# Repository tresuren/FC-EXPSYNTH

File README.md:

# FC-EXPSYNTH

ファミコン拡張音源カセット(VRC6/VRC7/N163)を本物のチップで鳴らす中継カートリッジ(RP2350B)。PCからUSB-MIDIで、将来はmicroSDのVGMで演奏する計画。

## 構成
- `hardware/<Rev>/` — リビジョンごとのKiCadプロジェクト(回路図・基板・フットプリント・BOM・docs・生成スクリプト)
- `firmware/` — RP2350ファーム(現在 stage1_bus_test)

## バージョン管理
- リビジョンはフォルダ(`hardware/RevE1/` など)で管理。大きな設計変更は新フォルダ(RevE2…)で行う。
- 現在: **RevE5(ドラフト)** — 92x80mm、PPU バスと /IRQ を上部スロットへ直結(上のカセットのゲームが動く想定)、ゲーム/演奏モード切替、データバス双方向(ゲーム中の音源書き込みを記録用に読める)、全部品表面実装。DRC 未接続0。詳細は `hardware/RevE5/README.md`。
- RevE4 — RevE3 の電源まわりを修正(L1 をチップ横へ、電源配線を太く)。`hardware/RevE4/README.md`。
- RevE3 — RevE2から microSD・USB-C を基板端へ移動(ケース用)。`hardware/RevE3/README.md`。
- RevE2 — 92x60mm、表面SMD+裏面7個手半田、配線完了。`hardware/RevE2/` に残す。
- 過去: RevE1 — 配線7本未接続のため RevE2 で置き換え。`hardware/RevE1/` に残す。

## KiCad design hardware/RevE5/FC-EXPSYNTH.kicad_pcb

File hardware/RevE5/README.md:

# FC-EXPSYNTH (Rev.E5 draft) — 92x80mm、PPU直結・ゲームモード・データバス双方向

RevE4 を作り直した版。基板を 20mm 高くして、上に刺したカセットのゲームが動くように画面系(PPU)の線を通し、ゲーム中の音源書き込みを RP2350 が読めるようにした。部品は全部表面(JLCPCB の片面実装で全部載る。手半田は J11 など差し込み・直付けの部品だけ)。

## RevE4 からの変更点

### 回路(`FC-EXPSYNTH.kicad_sch`、`scripts/gen_sch.py`)
- **PPU バス 27 本(J10/J11 の 17〜29、47〜60 番)と /IRQ(15 番)を J10(接触指)⇔ J11(上部スロット)で直結**。ネット名 `PPU_*`、`CIRAM_*`、`IRQ_N`。
- **ゲーム/演奏モード切替**: `GAME` = GPIO30(R51 1k 経由)、R52 10k で +3V3 にプルアップ(**既定=ゲームモード**)。
  - RW_SYN = R/W AND NOT GAME(U14 の空きゲート + U15 の空きインバータ)
  - ROMSEL_EXP(J11 44番) = ROMSEL_N OR RW_SYN → ゲームモードでは上のカセットに /ROMSEL がそのまま届く。演奏モード(GPIO30 = Low)では書き込みだけ届く(RevE4 と同じ動作)。
- **データバス双方向化**: U13 を 74AHCT245(5V)→ **74LVC245(3.3V、B 側は 5V 入力対応)** に変更、DIR = R/W(読み出し: RP2350→ファミコン、書き込み: ファミコン→RP2350)。
  - **U17(74LVC1G02、新規)**: OE_N = NOT(RW_N OR OE1)。CPU の書き込みサイクルは常に U13 が開き、RP2350 がデータを読める(ゲーム中の音源レジスタ書き込みの記録用)。$8000 以上の読み出しは従来どおり EN_N で RP2350 が応答。
  - RP2350 に 5V が入らない構成(U13 の A 側は 3.3V 出力)。ファミコン側への出力は 3.3V(TTL の High 2.0V 以上)。
  - **ファーム側の注意**: CPU の書き込みサイクル中は ED0〜7(GPIO19〜26)を入力にしておくこと(U13 が RP2350 側へ出力するため。330Ω で保護はある)。
- テストパッド: TP7 = GAME、TP8 = IRQ_N(RevE4 の D0/A0 から変更)。
- 部品追加: U17、C42(U17 のパスコン)、R51、R52。部品数 99。

### 基板(`FC-EXPSYNTH.kicad_pcb`)
- **92x60mm → 92x80mm**(本体 0〜69.3mm、接触指 69.3〜80mm)。バッファ IC の列を y=52mm に置き、接触指までの配線帯を約 4mm → 約 14mm に拡大。
- **PPU の 27 本は裏面にまっすぐな縦の線(0.15mm、ロック)**: 接触指の上と J11 の下でビアを使い、裏面で 2 本 1 組(各ピンの ±0.6mm)で通す(`scripts/ppu_lanes.py`)。PPU_D4(60番)だけ USB-C の固定端子を避けて少し迂回。
- **裏面の部品なし**(RevE4 の裏 7 個のコンデンサは表面の 0402 に)。
- **水晶 Y1 を RP2350 の XIN/XOUT(30/31 番ピン)の約 4mm 下**へ。L1(コア電源インダクタ)は RevE4 と同じくピン 63 の隣。
- 電源ネット(+5V、+3V3、+1V1、VSYS、VBUS)に Power ネットクラス 0.25mm を設定して配線し、空きのある区間を最大 0.5mm に拡幅(`scripts/widen.py`)。
  - +5V: 0.5mm 57mm / 0.4mm 47mm / 0.3mm 62mm / 0.25mm 91mm(**全区間 0.25mm 以上**)
  - +3V3: 内層 In2 の面 + 配線(0.22mm 2mm 以外は 0.25mm 以上)
  - +1V1: 0.25〜0.5mm、VREG_LX 約 2mm
- 基板の縁から 0.45mm は配線・ビア禁止(自動配線が縁の規則を守らないため)。
- 部品名の文字 0.8mm / 線幅 0.12mm。

## 状態(正直な現状)
- DRC(`docs/drc.rpt`): **未接続 0・クリアランス違反 0・短絡 0・穴間隔違反 0・禁止エリア違反 0・基板端違反 0・余り線 0**。残りは警告: silk_over_copper 36 / silk_overlap 27 / lib_footprint_issues 99 / courtyards_overlap 1(J10 と J4、以前から)。
- **水晶の配線長: XIN 約 11mm、XOUT 約 13mm、C4 側 約 17mm**(Y1 自体はピンの直下だが、自動配線が C4 と R2 を少し離れた場所に置いた)。下は全面 GND 層。RevE4(約 23mm)より短いが、理想(数 mm)ではない。水晶まわりを固定して配線する案も 3 回試したが、RP2350 下側が詰まって 2〜7 本つながらなかったため、この版を採用。発振は実機で確認が必要。
- **ERC(回路図のルール検査)は未実施**(この環境の KiCad 7 の CLI に ERC がないため)。KiCad で開いて確認してほしい。
- 74LVC245 を 3.3V で使い、ファミコンのバスへ 3.3V で出す設計。ファミコン実機での読み出しタイミング・電圧の余裕は実機で確認が必要。
- J11(上部スロット)のフットプリントは仮寸法のまま(実物の 2x30 コネクタで要確認)。microSD、USB-C の実物寸法も未確認。
- LCSC 部品番号、JLCPCB 見積り、ファーム(モード切替・書き込み記録)は未着手。
- 上のカセットでゲームを動かすには: GAME = High(既定)、EN_N = High(既定)のまま。演奏モードでは RP2350 が GPIO30 を Low にしてから、本体のリセットボタンを押す想定。

## 図面
- `docs/pcb_render.png`(表面)、`docs/pcb_render_back.png`(裏面、左右反転表示)、`docs/fc_sch.pdf`(回路図)、`docs/drc.rpt`(DRC)、`BOM.csv`(部品表、`scripts/make_bom.py` で基板から生成)

## 再生成
1. `python3 scripts/gen_sch.py` → `kicad-cli sch export netlist -o fc.net FC-EXPSYNTH.kicad_sch`
2. `scripts/build_all.sh`(部品配置 `build_pcb.py` → `.kicad_pro` の規則を戻す → `ppu_lanes.py`)
3. `FR_JAR=... scripts/run_fr.sh`(Freerouting で自動配線 → `route.ses`)→ `python3 scripts/imp.py`
4. `HARD=1 python3 scripts/route_fix6.py <dir>`(残りの補修) → `scripts/widen.py`(電源線を太く)
自動配線は実行ごとに結果が変わる。確定した配線はこのフォルダの `FC-EXPSYNTH.kicad_pcb` を正とする(+3V3 の 50 番ピンと GPIO36 は手で補修済み)。

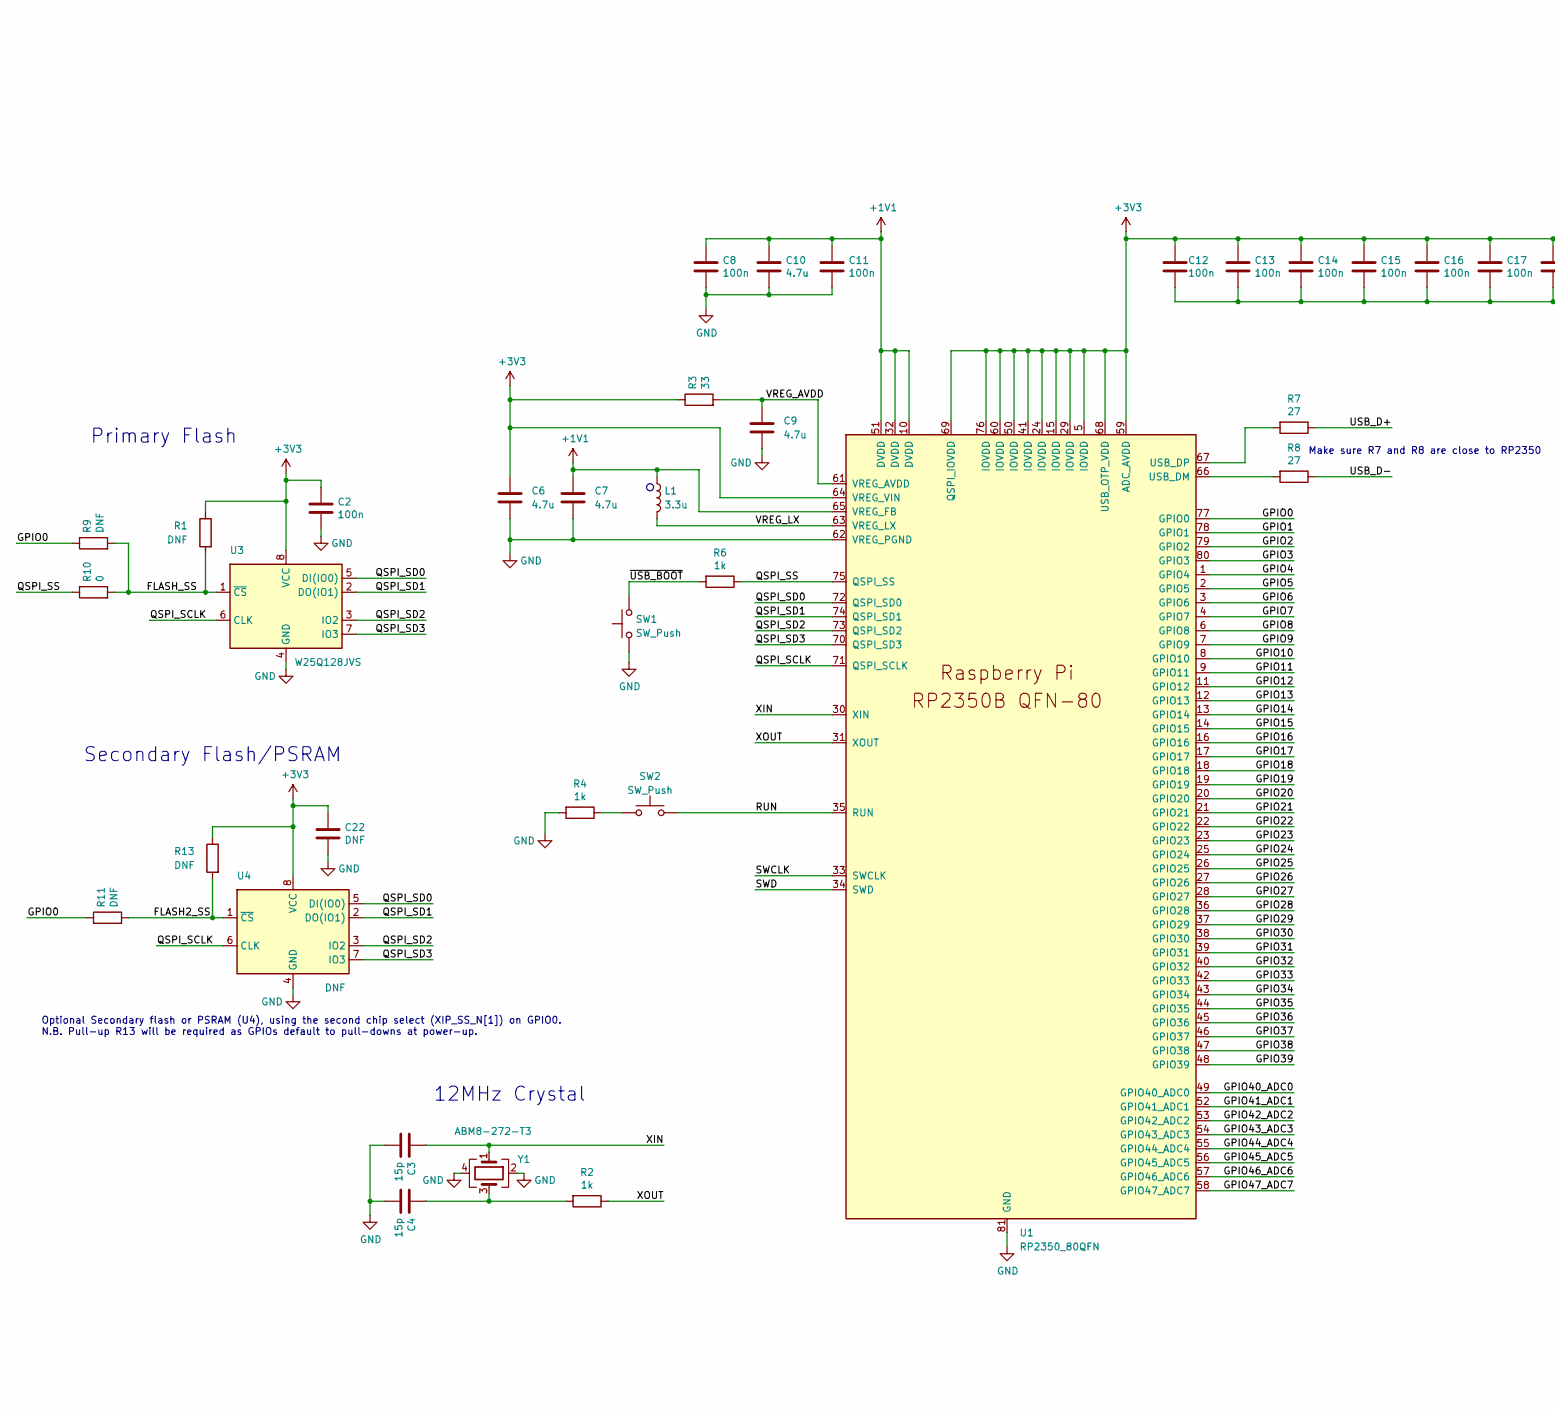
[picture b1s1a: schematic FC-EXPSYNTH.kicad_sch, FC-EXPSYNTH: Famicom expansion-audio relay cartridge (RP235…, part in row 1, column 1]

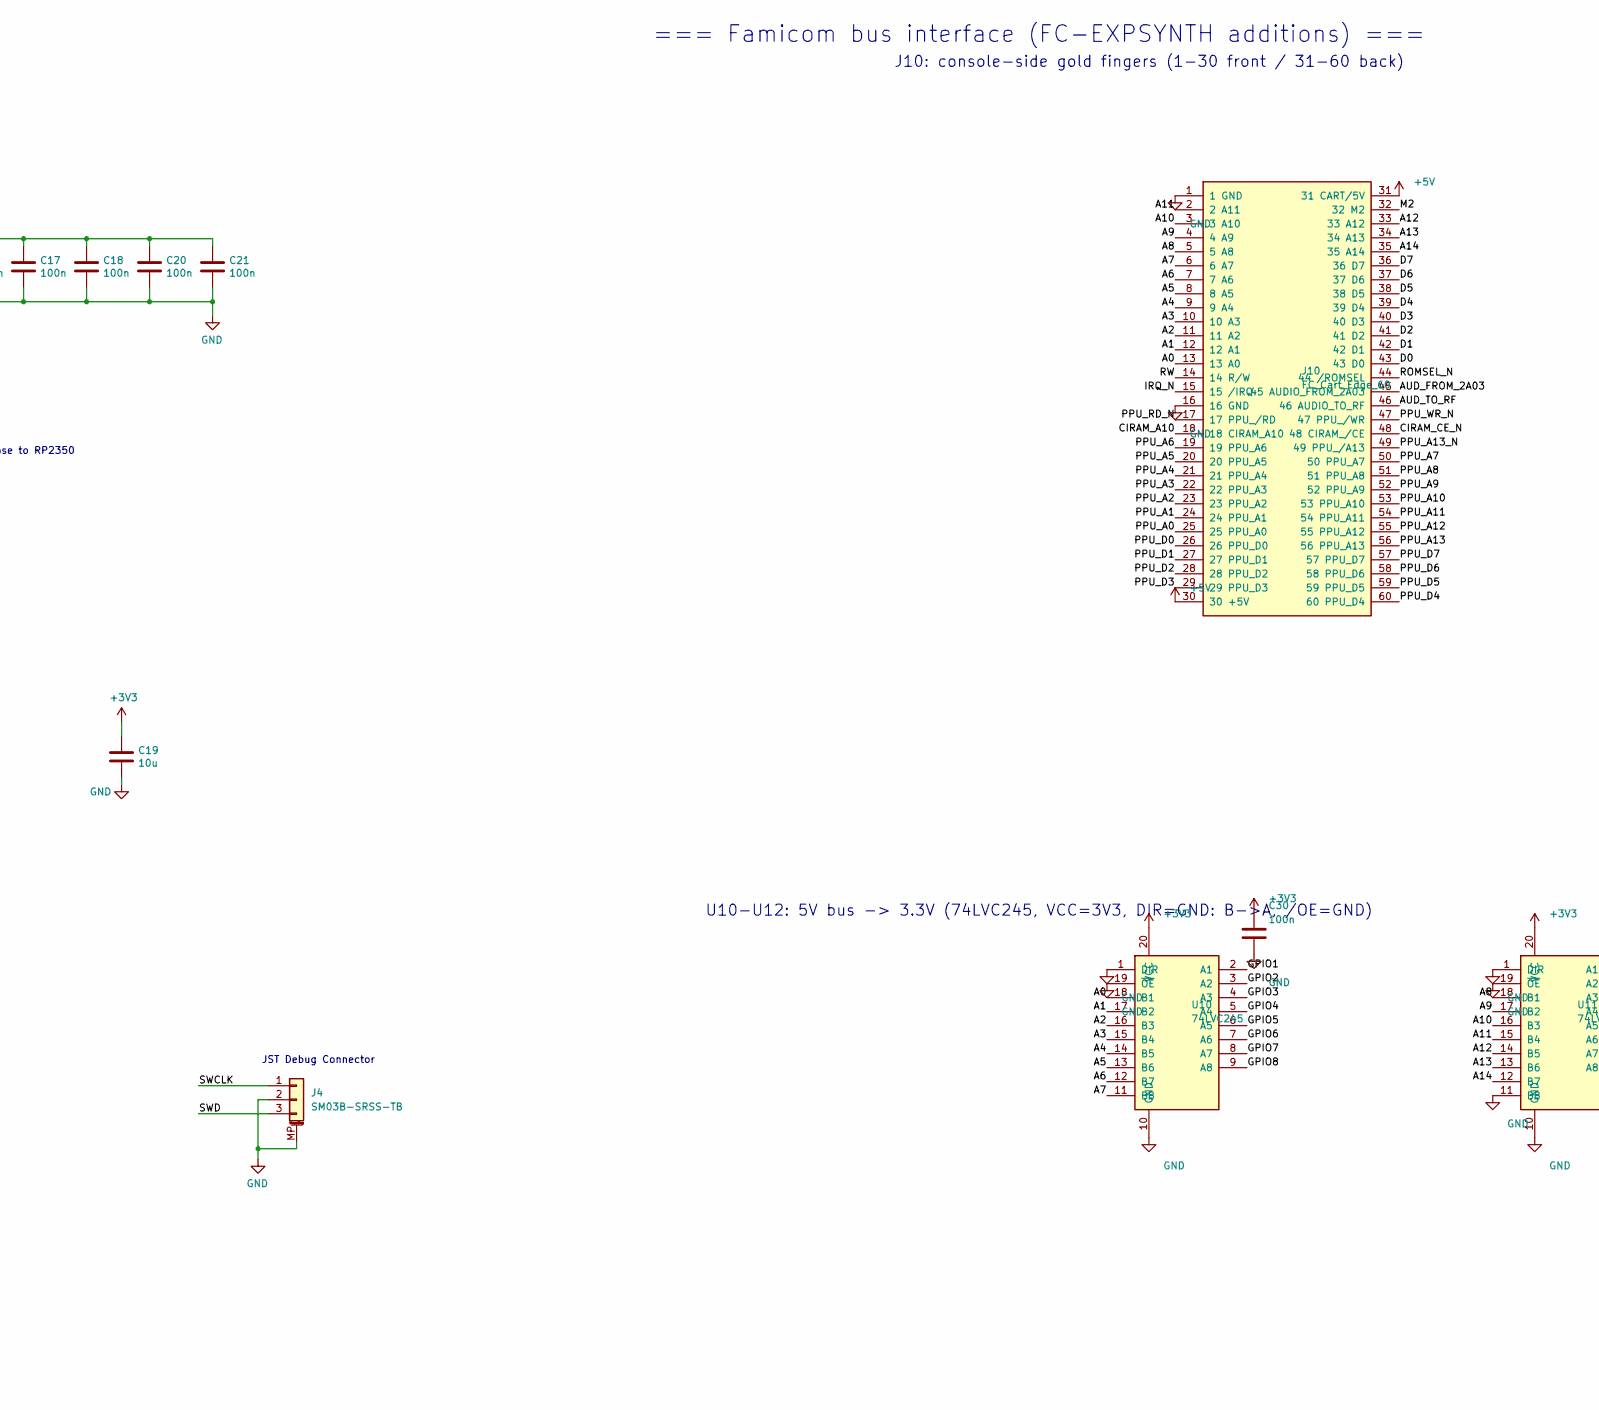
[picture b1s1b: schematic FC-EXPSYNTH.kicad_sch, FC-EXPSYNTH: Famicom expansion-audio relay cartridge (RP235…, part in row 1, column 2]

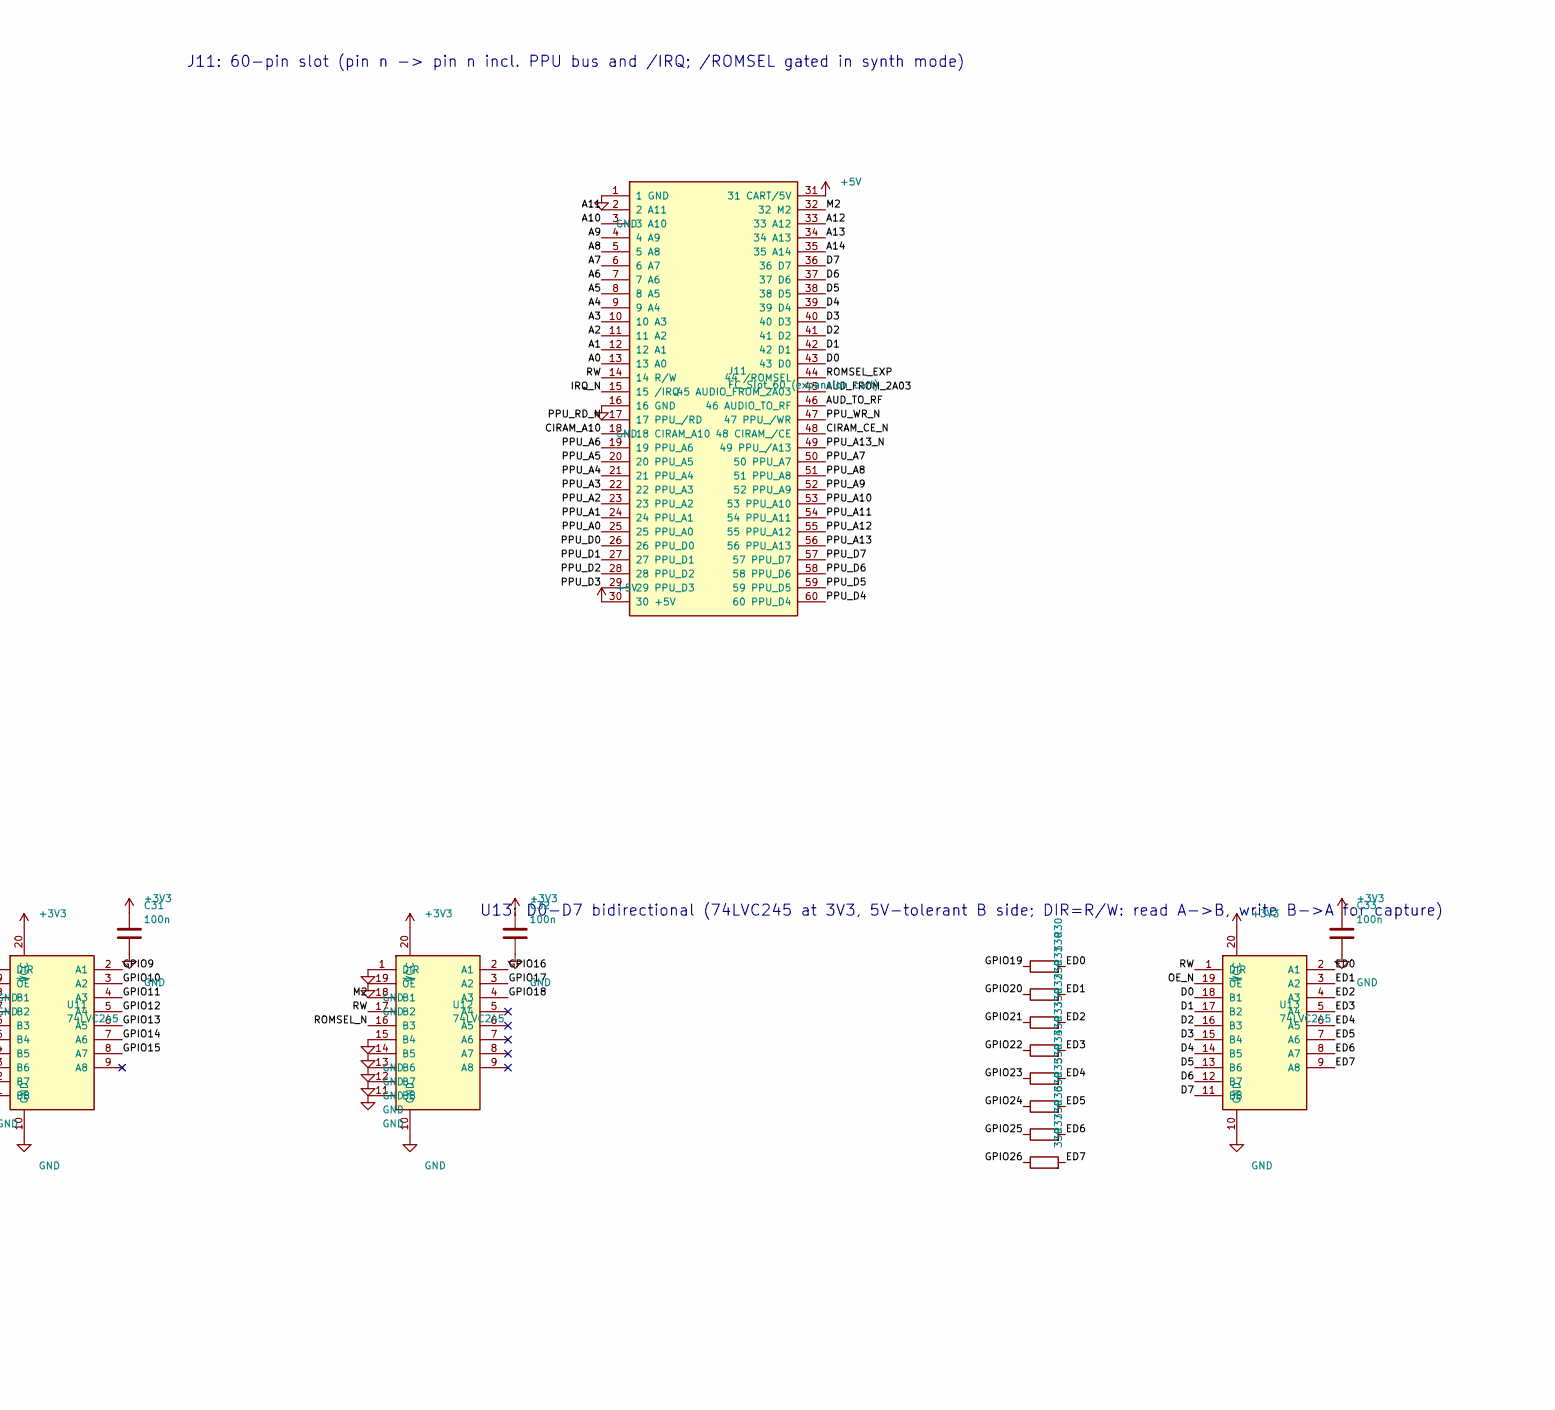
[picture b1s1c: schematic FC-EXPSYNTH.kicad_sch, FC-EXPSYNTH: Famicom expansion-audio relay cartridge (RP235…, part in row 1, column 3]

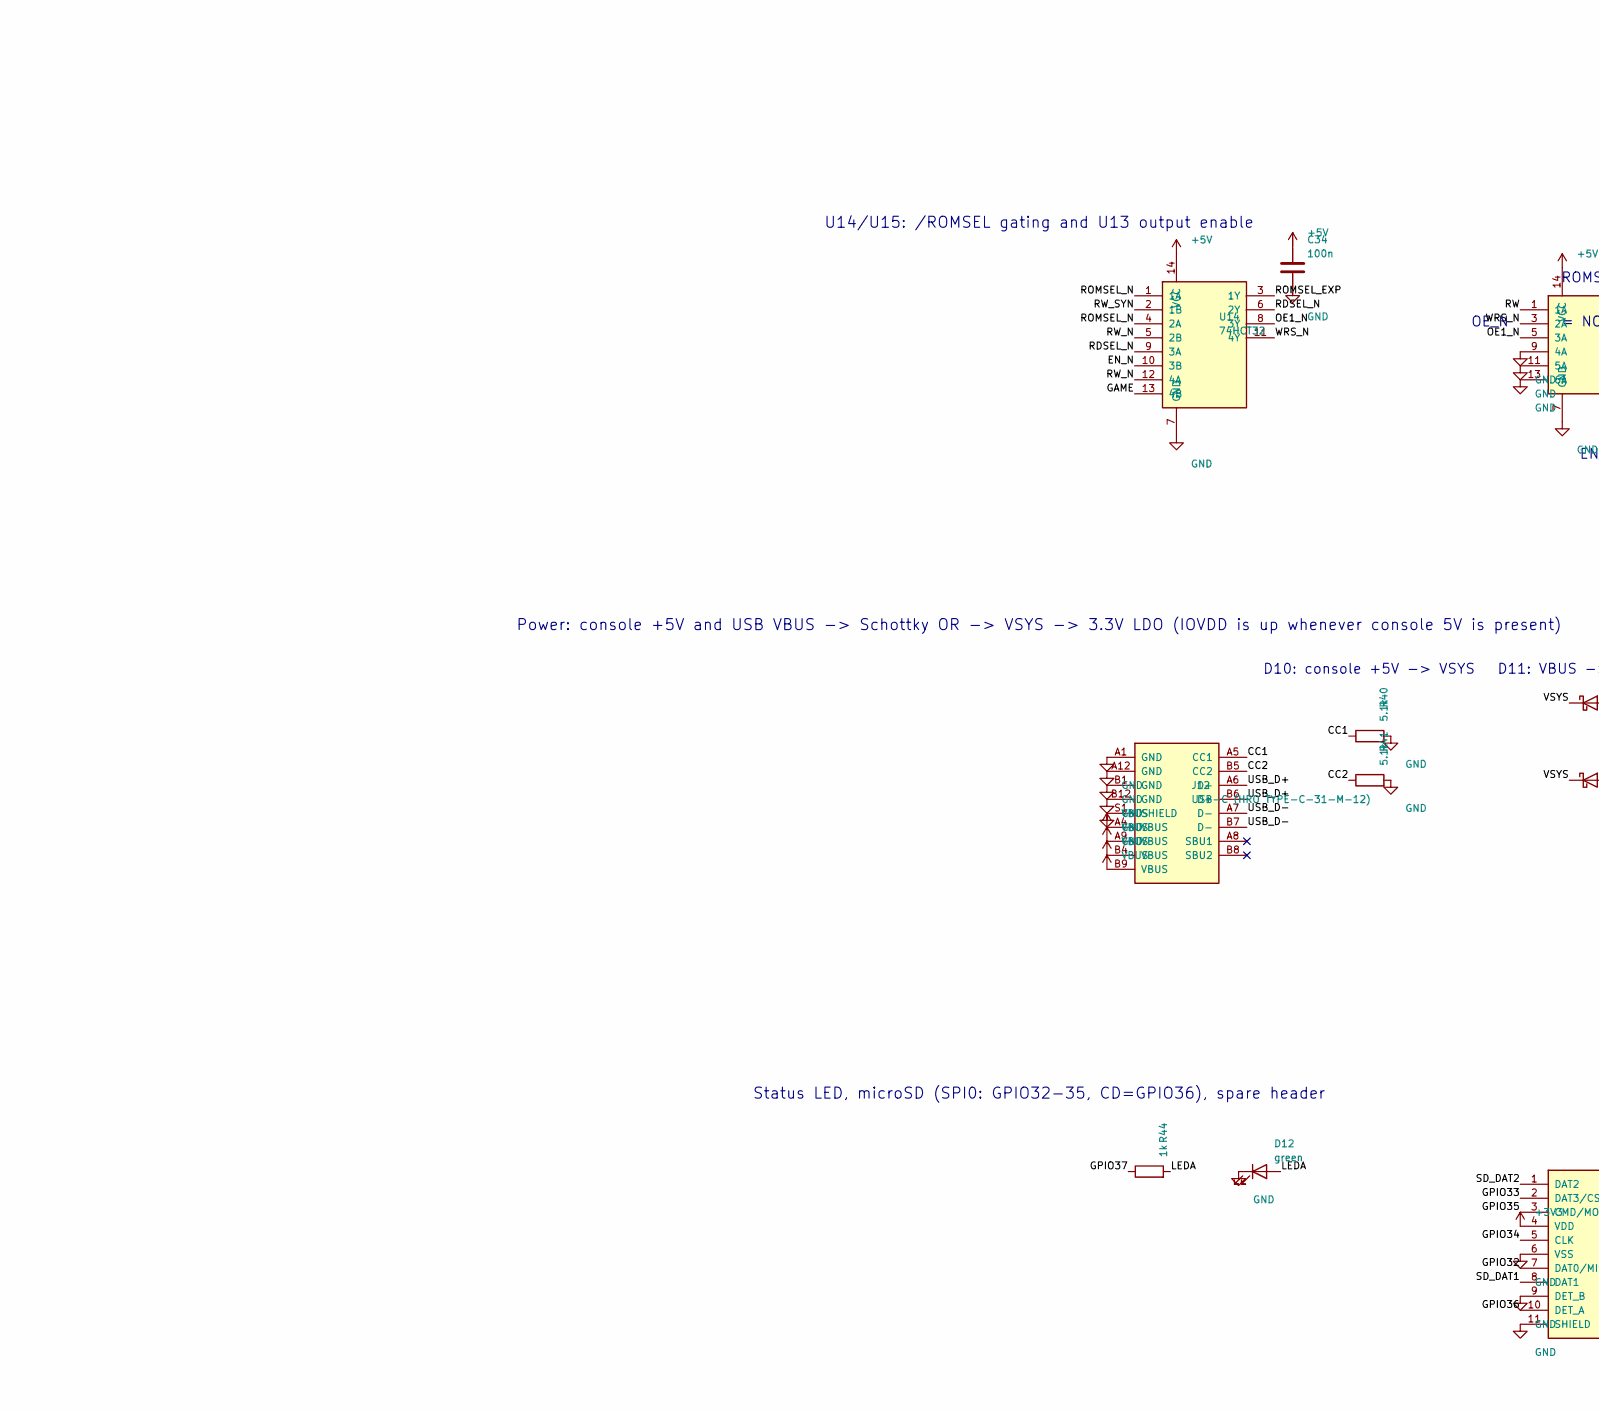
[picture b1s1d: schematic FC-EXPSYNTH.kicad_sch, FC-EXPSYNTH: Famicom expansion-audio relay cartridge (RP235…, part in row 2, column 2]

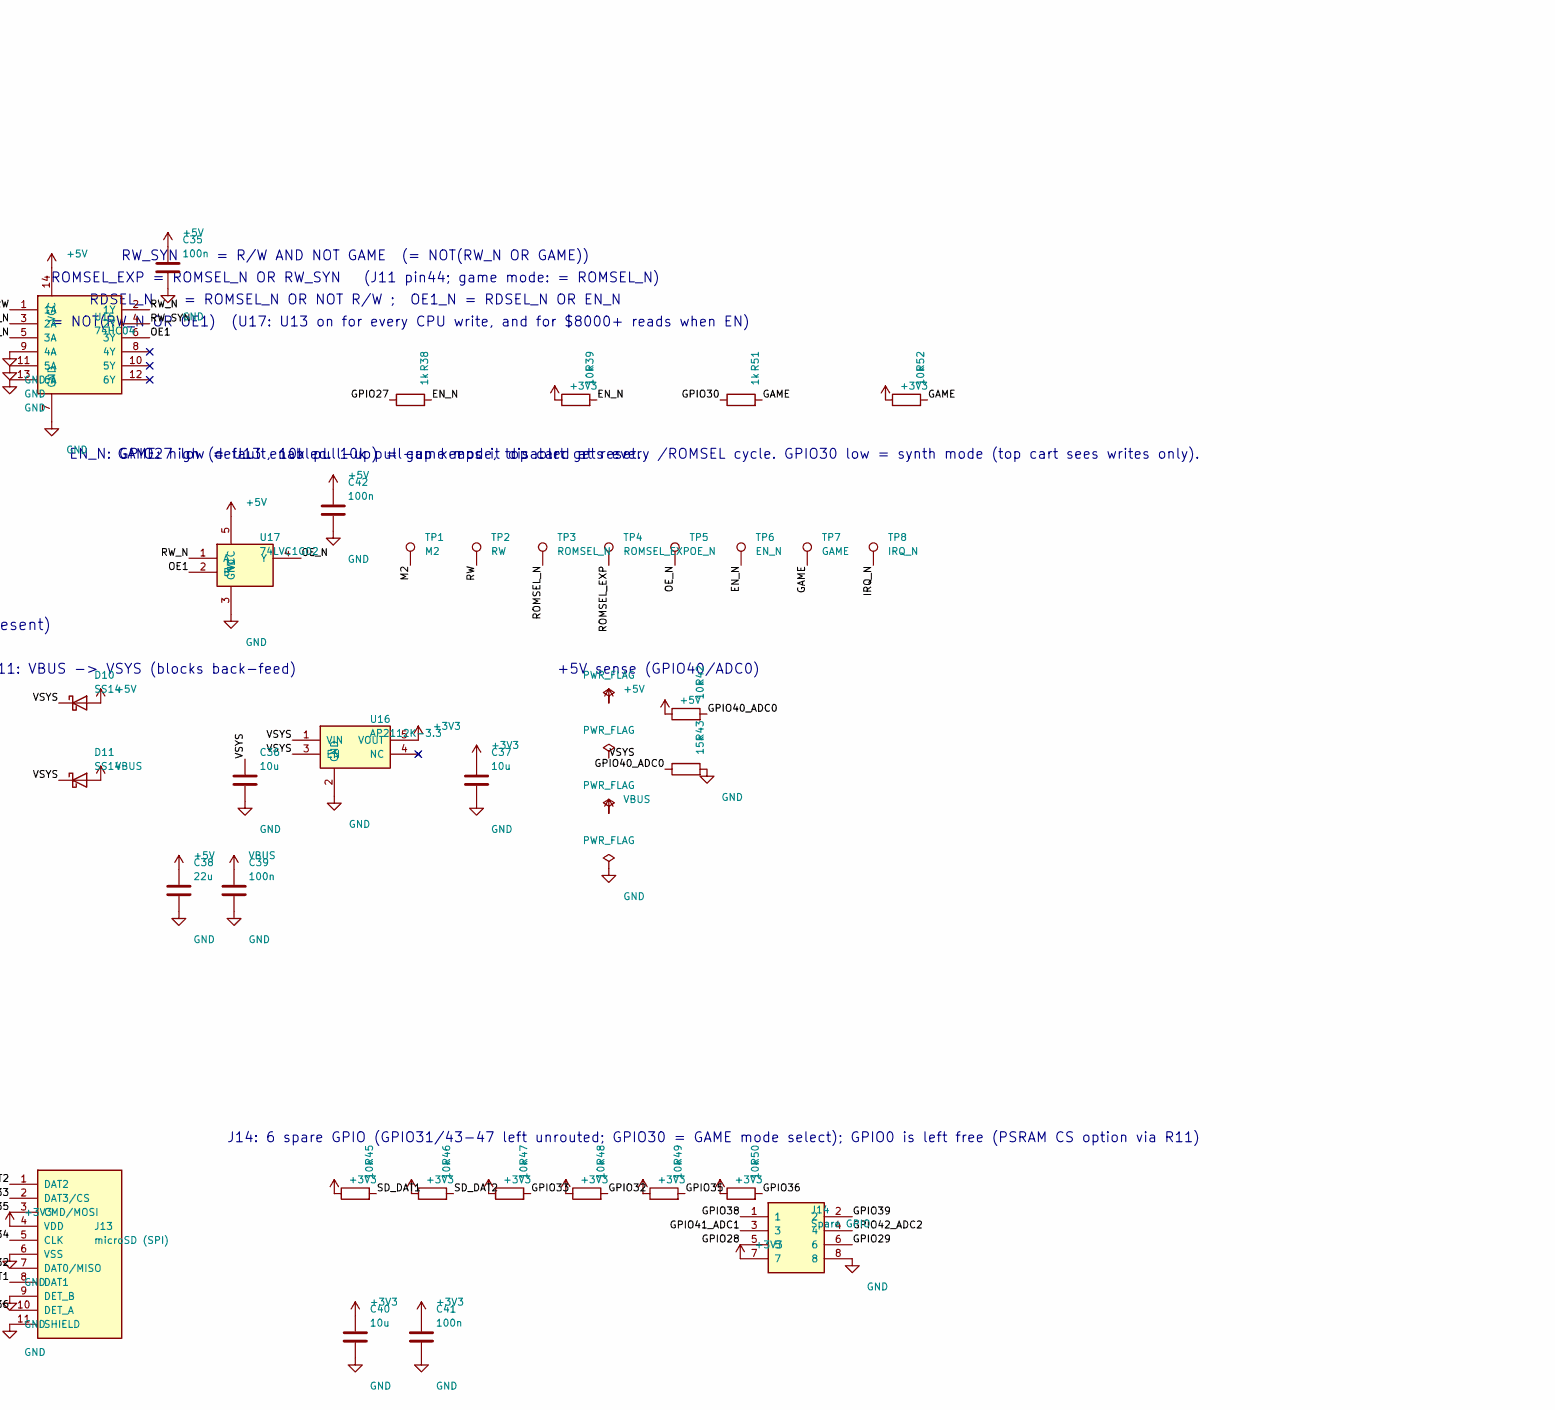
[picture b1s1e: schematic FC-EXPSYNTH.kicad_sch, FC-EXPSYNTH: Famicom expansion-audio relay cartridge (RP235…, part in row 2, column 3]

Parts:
C2, C8, C11, C12, C13, C14, C15, C16, C17, C18, C20, C21, C30, C31, C32, C33, C34, C35, C39, C41, C42: 100n; C_0402_1005Metric
C3, C4: 15p; C_0402_1005Metric
C6, C7: 4.7u; C_0402_1005Metric_small_pads
C9, C10: 4.7u; C_0402_1005Metric
C19, C36, C37, C40: 10u; C_0805_2012Metric
C22: DNF; C_0402_1005Metric
C38: 22u; C_0805_2012Metric
D10, D11: SS14; D_SMA
D12: green; LED_0603_1608Metric
J4: SM03B-SRSS-TB; JST_SH_SM03B-SRSS-TB_1x03-1MP_P1.00mm_Horizontal
J10: FC_Cart_Edge_60
J11: FC_Slot_60 (expansion cart); FC_Slot_60
J12: USB-C (HRO TYPE-C-31-M-12); USB_C_Receptacle_HRO_TYPE-C-31-M-12
J13: microSD (SPI); microSD_HC_Hirose_DM3AT-SF-PEJM5
J14: Spare GPIO; PinHeader_2x04_P2.54mm_Vertical
L1: 3.3u; L_pol_2016
R1, R9, R11, R13: DNF; R_0402_1005Metric
R2, R4, R6, R38, R44, R51: 1k; R_0402_1005Metric
R3: 33; R_0402_1005Metric
R7, R8: 27; R_0402_1005Metric
R10: 0; R_0402_1005Metric
R30, R31, R32, R33, R34, R35, R36, R37: 330; R_0402_1005Metric
R39, R42, R45, R46, R47, R48, R49, R50, R52: 10k; R_0402_1005Metric
R40, R41: 5.1k; R_0402_1005Metric
R43: 15k; R_0402_1005Metric
SW1, SW2: SW_Push; SW_Push_1P1T_NO_Vertical_Wuerth_434133025816
TP1: M2; TestPoint_Pad_D1.0mm
TP2: RW; TestPoint_Pad_D1.0mm
TP3: ROMSEL_N; TestPoint_Pad_D1.0mm
TP4: ROMSEL_EXP; TestPoint_Pad_D1.0mm
TP5: OE_N; TestPoint_Pad_D1.0mm
TP6: EN_N; TestPoint_Pad_D1.0mm
TP7: GAME; TestPoint_Pad_D1.0mm
TP8: IRQ_N; TestPoint_Pad_D1.0mm
U1: RP2350_80QFN; RP2350-QFN-80-1EP_10x10_P0.4mm_EP3.4x3.4mm_ThermalVias
U3: W25Q128JVS; SOIC-8_5.23x5.23mm_P1.27mm
U4: DNF; SOIC-8_5.23x5.23mm_P1.27mm
U10, U11, U12, U13: 74LVC245; TSSOP-20_4.4x6.5mm_P0.65mm
U14: 74HCT32; TSSOP-14_4.4x5mm_P0.65mm
U15: 74HC04; TSSOP-14_4.4x5mm_P0.65mm
U16: AP2112K-3.3; SOT-23-5
U17: 74LVC1G02; SOT-23-5
Y1: ABM8-272-T3; Crystal_SMD_3225-4Pin_3.2x2.5mm

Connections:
+1V1: C7.1, C8.1, C10.1, C11.1, L1.1, U1.10 (DVDD), U1.32 (DVDD), U1.51 (DVDD), U1.65 (VREG_FB)
+3V3: C2.1, C6.1, C12.1, C13.1, C14.1, C15.1, C16.1, C17.1, C18.1, C19.1, C20.1, C21.1, C22.1, C30.1, C31.1, C32.1, C33.1, C37.1, C40.1, C41.1, J13.4 (VDD), J14.7, R1.1, R3.1, R13.1, R39.1, R45.1, R46.1, R47.1, R48.1, R49.1, R50.1, R52.1, U1.5 (IOVDD), U1.15 (IOVDD), U1.24 (IOVDD), U1.29 (IOVDD), U1.41 (IOVDD), U1.50 (IOVDD), U1.59 (ADC_AVDD), U1.60 (IOVDD), U1.64 (VREG_VIN), U1.68 (USB_OTP_VDD), U1.69 (QSPI_IOVDD), U1.76 (IOVDD), U3.8 (VCC), U4.8 (VCC), U10.20 (VCC), U11.20 (VCC), U12.20 (VCC), U13.20 (VCC), U16.5 (VOUT)
+5V: C34.1, C35.1, C38.1, C42.1, D10.2 (A), J10.30 (30 +5V), J10.31 (31 CART/5V), J11.30 (30 +5V), J11.31 (31 CART/5V), R42.1, U14.14 (VCC), U15.14 (VCC), U17.5 (VCC)
/A0: J10.13 (13 A0), J11.13 (13 A0), U10.18 (B1)
/A1: J10.12 (12 A1), J11.12 (12 A1), U10.17 (B2)
/A2: J10.11 (11 A2), J11.11 (11 A2), U10.16 (B3)
/A3: J10.10 (10 A3), J11.10 (10 A3), U10.15 (B4)
/A4: J10.9 (9 A4), J11.9 (9 A4), U10.14 (B5)
/A5: J10.8 (8 A5), J11.8 (8 A5), U10.13 (B6)
/A6: J10.7 (7 A6), J11.7 (7 A6), U10.12 (B7)
/A7: J10.6 (6 A7), J11.6 (6 A7), U10.11 (B8)
/A8: J10.5 (5 A8), J11.5 (5 A8), U11.18 (B1)
/A9: J10.4 (4 A9), J11.4 (4 A9), U11.17 (B2)
/A10: J10.3 (3 A10), J11.3 (3 A10), U11.16 (B3)
/A11: J10.2 (2 A11), J11.2 (2 A11), U11.15 (B4)
/A12: J10.33 (33 A12), J11.33 (33 A12), U11.14 (B5)
/A13: J10.34 (34 A13), J11.34 (34 A13), U11.13 (B6)
/A14: J10.35 (35 A14), J11.35 (35 A14), U11.12 (B7)
/AUD_FROM_2A03: J10.45 (45 AUDIO_FROM_2A03), J11.45 (45 AUDIO_FROM_2A03)
/AUD_TO_RF: J10.46 (46 AUDIO_TO_RF), J11.46 (46 AUDIO_TO_RF)
/CC1: J12.A5 (CC1), R40.1
/CC2: J12.B5 (CC2), R41.1
/CIRAM_A10: J10.18 (18 CIRAM_A10), J11.18 (18 CIRAM_A10)
/CIRAM_CE_N: J10.48 (48 CIRAM_/CE), J11.48 (48 CIRAM_/CE)
/D0: J10.43 (43 D0), J11.43 (43 D0), U13.18 (B1)
/D1: J10.42 (42 D1), J11.42 (42 D1), U13.17 (B2)
/D2: J10.41 (41 D2), J11.41 (41 D2), U13.16 (B3)
/D3: J10.40 (40 D3), J11.40 (40 D3), U13.15 (B4)
/D4: J10.39 (39 D4), J11.39 (39 D4), U13.14 (B5)
/D5: J10.38 (38 D5), J11.38 (38 D5), U13.13 (B6)
/D6: J10.37 (37 D6), J11.37 (37 D6), U13.12 (B7)
/D7: J10.36 (36 D7), J11.36 (36 D7), U13.11 (B8)
/ED0: R30.2, U13.2 (A1)
/ED1: R31.2, U13.3 (A2)
/ED2: R32.2, U13.4 (A3)
/ED3: R33.2, U13.5 (A4)
/ED4: R34.2, U13.6 (A5)
/ED5: R35.2, U13.7 (A6)
/ED6: R36.2, U13.8 (A7)
/ED7: R37.2, U13.9 (A8)
/EN_N: R38.2, R39.2, TP6.1, U14.10 (3B)
/FLASH2_SS: R11.2, R13.2, U4.1 (~CS)
/FLASH_SS: R1.2, R9.2, R10.2, U3.1 (~CS)
/GAME: R51.2, R52.2, TP7.1, U14.13 (4B)
/GPIO0: R9.1, R11.1, U1.77 (GPIO0)
/GPIO1: U1.78 (GPIO1), U10.2 (A1)
/GPIO2: U1.79 (GPIO2), U10.3 (A2)
/GPIO3: U1.80 (GPIO3), U10.4 (A3)
/GPIO4: U1.1 (GPIO4), U10.5 (A4)
/GPIO5: U1.2 (GPIO5), U10.6 (A5)
/GPIO6: U1.3 (GPIO6), U10.7 (A6)
/GPIO7: U1.4 (GPIO7), U10.8 (A7)
/GPIO8: U1.6 (GPIO8), U10.9 (A8)
/GPIO9: U1.7 (GPIO9), U11.2 (A1)
/GPIO10: U1.8 (GPIO10), U11.3 (A2)
/GPIO11: U1.9 (GPIO11), U11.4 (A3)
/GPIO12: U1.11 (GPIO12), U11.5 (A4)
/GPIO13: U1.12 (GPIO13), U11.6 (A5)
/GPIO14: U1.13 (GPIO14), U11.7 (A6)
/GPIO15: U1.14 (GPIO15), U11.8 (A7)
/GPIO16: U1.16 (GPIO16), U12.2 (A1)
/GPIO17: U1.17 (GPIO17), U12.3 (A2)
/GPIO18: U1.18 (GPIO18), U12.4 (A3)
/GPIO19: R30.1, U1.19 (GPIO19)
/GPIO20: R31.1, U1.20 (GPIO20)
/GPIO21: R32.1, U1.21 (GPIO21)
/GPIO22: R33.1, U1.22 (GPIO22)
/GPIO23: R34.1, U1.23 (GPIO23)
/GPIO24: R35.1, U1.25 (GPIO24)
/GPIO25: R36.1, U1.26 (GPIO25)
/GPIO26: R37.1, U1.27 (GPIO26)
/GPIO27: R38.1, U1.28 (GPIO27)
/GPIO28: J14.5, U1.36 (GPIO28)
/GPIO29: J14.6, U1.37 (GPIO29)
/GPIO30: R51.1, U1.38 (GPIO30)
/GPIO31: U1.39 (GPIO31)
/GPIO32: J13.7 (DAT0/MISO), R48.2, U1.40 (GPIO32)
/GPIO33: J13.2 (DAT3/CS), R47.2, U1.42 (GPIO33)
/GPIO34: J13.5 (CLK), U1.43 (GPIO34)
/GPIO35: J13.3 (CMD/MOSI), R49.2, U1.44 (GPIO35)
/GPIO36: J13.10 (DET_A), R50.2, U1.45 (GPIO36)
/GPIO37: R44.1, U1.46 (GPIO37)
/GPIO38: J14.1, U1.47 (GPIO38)
/GPIO39: J14.2, U1.48 (GPIO39)
/GPIO40_ADC0: R42.2, R43.1, U1.49 (GPIO40_ADC0)
/GPIO41_ADC1: J14.3, U1.52 (GPIO41_ADC1)
/GPIO42_ADC2: J14.4, U1.53 (GPIO42_ADC2)
/GPIO43_ADC3: U1.54 (GPIO43_ADC3)
/GPIO44_ADC4: U1.55 (GPIO44_ADC4)
/GPIO45_ADC5: U1.56 (GPIO45_ADC5)
/GPIO46_ADC6: U1.57 (GPIO46_ADC6)
/GPIO47_ADC7: U1.58 (GPIO47_ADC7)
/IRQ_N: J10.15 (15 /IRQ), J11.15 (15 /IRQ), TP8.1
/LEDA: D12.2 (A), R44.2
/M2: J10.32 (32 M2), J11.32 (32 M2), TP1.1, U12.18 (B1)
/OE1: U15.6 (3Y), U17.2 (B)
/OE1_N: U14.8 (3Y), U15.5 (3A)
/OE_N: TP5.1, U13.19 (~OE), U17.4 (Y)
/PPU_A0: J10.25 (25 PPU_A0), J11.25 (25 PPU_A0)
/PPU_A1: J10.24 (24 PPU_A1), J11.24 (24 PPU_A1)
/PPU_A2: J10.23 (23 PPU_A2), J11.23 (23 PPU_A2)
/PPU_A3: J10.22 (22 PPU_A3), J11.22 (22 PPU_A3)
/PPU_A4: J10.21 (21 PPU_A4), J11.21 (21 PPU_A4)
/PPU_A5: J10.20 (20 PPU_A5), J11.20 (20 PPU_A5)
/PPU_A6: J10.19 (19 PPU_A6), J11.19 (19 PPU_A6)
/PPU_A7: J10.50 (50 PPU_A7), J11.50 (50 PPU_A7)
/PPU_A8: J10.51 (51 PPU_A8), J11.51 (51 PPU_A8)
/PPU_A9: J10.52 (52 PPU_A9), J11.52 (52 PPU_A9)
/PPU_A10: J10.53 (53 PPU_A10), J11.53 (53 PPU_A10)
/PPU_A11: J10.54 (54 PPU_A11), J11.54 (54 PPU_A11)
/PPU_A12: J10.55 (55 PPU_A12), J11.55 (55 PPU_A12)
/PPU_A13: J10.56 (56 PPU_A13), J11.56 (56 PPU_A13)
/PPU_A13_N: J10.49 (49 PPU_/A13), J11.49 (49 PPU_/A13)
/PPU_D0: J10.26 (26 PPU_D0), J11.26 (26 PPU_D0)
/PPU_D1: J10.27 (27 PPU_D1), J11.27 (27 PPU_D1)
/PPU_D2: J10.28 (28 PPU_D2), J11.28 (28 PPU_D2)
/PPU_D3: J10.29 (29 PPU_D3), J11.29 (29 PPU_D3)
/PPU_D4: J10.60 (60 PPU_D4), J11.60 (60 PPU_D4)
/PPU_D5: J10.59 (59 PPU_D5), J11.59 (59 PPU_D5)
/PPU_D6: J10.58 (58 PPU_D6), J11.58 (58 PPU_D6)
/PPU_D7: J10.57 (57 PPU_D7), J11.57 (57 PPU_D7)
/PPU_RD_N: J10.17 (17 PPU_/RD), J11.17 (17 PPU_/RD)
/PPU_WR_N: J10.47 (47 PPU_/WR), J11.47 (47 PPU_/WR)
/QSPI_SCLK: U1.71 (QSPI_SCLK), U3.6 (CLK), U4.6 (CLK)
/QSPI_SD0: U1.72 (QSPI_SD0), U3.5 (DI(IO0)), U4.5 (DI(IO0))
/QSPI_SD1: U1.74 (QSPI_SD1), U3.2 (DO(IO1)), U4.2 (DO(IO1))
/QSPI_SD2: U1.73 (QSPI_SD2), U3.3 (IO2), U4.3 (IO2)
/QSPI_SD3: U1.70 (QSPI_SD3), U3.7 (IO3), U4.7 (IO3)
/QSPI_SS: R6.1, R10.1, U1.75 (QSPI_SS)
/RDSEL_N: U14.6 (2Y), U14.9 (3A)
/ROMSEL_EXP: J11.44 (44 /ROMSEL), TP4.1, U14.3 (1Y)
/ROMSEL_N: J10.44 (44 /ROMSEL), TP3.1, U12.16 (B3), U14.1 (1A), U14.4 (2A)
/RUN: SW2.2, U1.35 (RUN)
/RW: J10.14 (14 R/W), J11.14 (14 R/W), TP2.1, U12.17 (B2), U13.1 (DIR), U15.1 (1A)
/RW_N: U14.5 (2B), U14.12 (4A), U15.2 (1Y), U17.1 (A)
/RW_SYN: U14.2 (1B), U15.4 (2Y)
/SD_DAT1: J13.8 (DAT1), R45.2
/SD_DAT2: J13.1 (DAT2), R46.2
/SWCLK: J4.1, U1.33 (SWCLK)
/SWD: J4.3, U1.34 (SWD)
/USB_D+: J12.A6 (D+), J12.B6 (D+), R7.1
/USB_D-: J12.A7 (D-), J12.B7 (D-), R8.1
/VREG_AVDD: C9.1, R3.2, U1.61 (VREG_AVDD)
/VREG_LX: L1.2, U1.63 (VREG_LX)
/VSYS: C36.1, D10.1 (K), D11.1 (K), U16.1 (VIN), U16.3 (EN)
/WRS_N: U14.11 (4Y), U15.3 (2A)
/XIN: C3.1, U1.30 (XIN), Y1.1
/XOUT: R2.1, U1.31 (XOUT)
/~USB_BOOT: R6.2, SW1.2
GND: C2.2, C3.2, C4.2, C6.2, C7.2, C8.2, C9.2, C10.2, C11.2, C12.2, C13.2, C14.2, C15.2, C16.2, C17.2, C18.2, C19.2, C20.2, C21.2, C22.2, C30.2, C31.2, C32.2, C33.2, C34.2, C35.2, C36.2, C37.2, C38.2, C39.2, C40.2, C41.2, C42.2, D12.1 (K), J4.2, J4.MP (MountPin), J10.1 (1 GND), J10.16 (16 GND), J11.1 (1 GND), J11.16 (16 GND), J12.A1 (GND), J12.A12 (GND), J12.B1 (GND), J12.B12 (GND), J12.S1 (SHIELD), J13.6 (VSS), J13.9 (DET_B), J13.11 (SHIELD), J14.8, R4.2, R40.2, R41.2, R43.2, SW1.1, U1.62 (VREG_PGND), U1.81 (GND), U3.4 (GND), U4.4 (GND), U10.1 (DIR), U10.10 (GND), U10.19 (~OE), U11.1 (DIR), U11.10 (GND), U11.11 (B8), U11.19 (~OE), U12.1 (DIR), U12.10 (GND), U12.11 (B8), U12.12 (B7), U12.13 (B6), U12.14 (B5), U12.15 (B4), U12.19 (~OE), U13.10 (GND), U14.7 (GND), U15.7 (GND), U15.9 (4A), U15.11 (5A), U15.13 (6A), U16.2 (GND), U17.3 (GND), Y1.2, Y1.4
unnamed: C4.1, R2.2, Y1.3
unnamed: R4.1, SW2.1
unnamed: R8.2, U1.66 (USB_DM)
unnamed: R7.2, U1.67 (USB_DP)
VBUS: C39.1, D11.2 (A), J12.A4 (VBUS), J12.A9 (VBUS), J12.B4 (VBUS), J12.B9 (VBUS)

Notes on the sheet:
Optional Secondary flash or PSRAM (U4), using the second chip select (XIP_SS_N[1]) on GPIO0. N.B. Pull-up R13 will be required as GPIOs default to pull-downs at power-up.
12MHz Crystal
Primary Flash
JST Debug Connector
Make sure R7 and R8 are close to RP2350
Secondary Flash/PSRAM
=== Famicom bus interface (FC-EXPSYNTH additions) ===
J10: console-side gold fingers (1-30 front / 31-60 back)
J11: 60-pin slot (pin n -> pin n incl. PPU bus and /IRQ; /ROMSEL gated in synth mode)
U10-U12: 5V bus -> 3.3V (74LVC245, VCC=3V3, DIR=GND: B->A, /OE=GND)
U13: D0-D7 bidirectional (74LVC245 at 3V3, 5V-tolerant B side; DIR=R/W: read A->B, write B->A for capture)
U14/U15: /ROMSEL gating and U13 output enable
GAME: high (default, 10k pull-up) = game mode, top cart gets every /ROMSEL cycle. GPIO30 low = synth mode (top cart sees writes only).
RW_SYN = R/W AND NOT GAME (= NOT(RW_N OR GAME))
ROMSEL_EXP = ROMSEL_N OR RW_SYN (J11 pin44; game mode: = ROMSEL_N)
RDSEL_N = ROMSEL_N OR NOT R/W ; OE1_N = RDSEL_N OR EN_N
OE_N = NOT(RW_N OR OE1) (U17: U13 on for every CPU write, and for $8000+ reads when EN)
EN_N: GPIO27 low = U13 enabled. 10k pull-up keeps it disabled at reset.
Power: console +5V and USB VBUS -> Schottky OR -> VSYS -> 3.3V LDO (IOVDD is up whenever console 5V is present)
D10: console +5V -> VSYS D11: VBUS -> VSYS (blocks back-feed)
+5V sense (GPIO40/ADC0)
Status LED, microSD (SPI0: GPIO32-35, CD=GPIO36), spare header
J14: 6 spare GPIO (GPIO31/43-47 left unrouted; GPIO30 = GAME mode select); GPIO0 is left free (PSRAM CS option via R11)

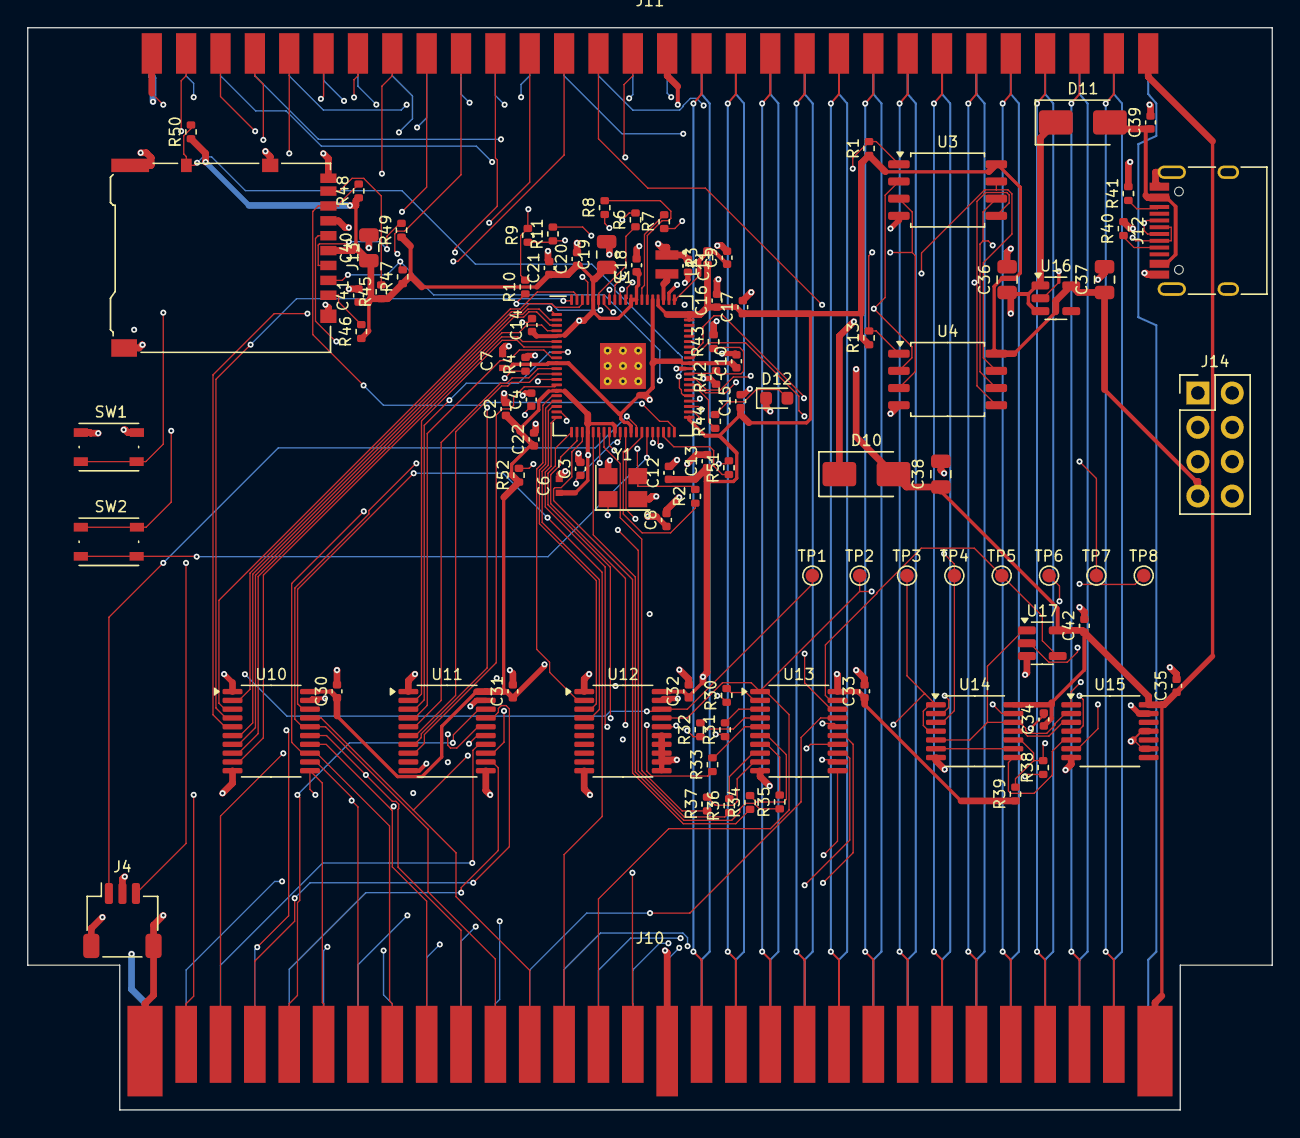
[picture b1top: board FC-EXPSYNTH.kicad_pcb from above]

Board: 4 copper layers, 92.0 x 80.0 mm, 99 parts (0 on the bottom side), 149 nets.

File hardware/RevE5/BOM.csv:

Designators,Qty,Value,Footprint,MPN/LCSC (UNVERIFIED - choose yourself)
C2 C8 C11 C12 C13 C14 C15 C16 C17 C18 C20 C21 C30 C31 C32 C33 C34 C35 C39 C41 C42,21,100n,C_0402_1005Metric,
C3 C4,2,15p,C_0402_1005Metric,
C6 C7,2,4.7u,C_0402_1005Metric_small_pads,
C9 C10,2,4.7u,C_0402_1005Metric,
C19 C36 C37 C40,4,10u,C_0805_2012Metric,
C22,1,DNF,C_0402_1005Metric,
C38,1,22u,C_0805_2012Metric,
D10 D11,2,SS14,D_SMA,
D12,1,green,LED_0603_1608Metric,
J4,1,SM03B-SRSS-TB,JST_SH_SM03B-SRSS-TB_1x03-1MP_P1.00mm_Horizontal,
J10,1,FC_Cart_Edge_60,FC_Cart_Edge_60,
J11,1,FC_Slot_60 (expansion cart),FC_Slot_60,hand-solder
J12,1,USB-C (HRO TYPE-C-31-M-12),USB_C_Receptacle_HRO_TYPE-C-31-M-12,
J13,1,microSD (SPI),microSD_HC_Hirose_DM3AT-SF-PEJM5,
J14,1,Spare GPIO,PinHeader_2x04_P2.54mm_Vertical,
L1,1,3.3u,L_pol_2016,
R1 R9 R11 R13,4,DNF,R_0402_1005Metric,
R2 R4 R6 R38 R44 R51,6,1k,R_0402_1005Metric,
R3,1,33,R_0402_1005Metric,
R7 R8,2,27,R_0402_1005Metric,
R10,1,0,R_0402_1005Metric,
R30 R31 R32 R33 R34 R35 R36 R37,8,330,R_0402_1005Metric,
R39 R42 R45 R46 R47 R48 R49 R50 R52,9,10k,R_0402_1005Metric,
R40 R41,2,5.1k,R_0402_1005Metric,
R43,1,15k,R_0402_1005Metric,
SW1 SW2,2,SW_Push,SW_Push_1P1T_NO_Vertical_Wuerth_434133025816,
TP1,1,M2,TestPoint_Pad_D1.0mm,not assembled (pads only)
TP2,1,RW,TestPoint_Pad_D1.0mm,not assembled (pads only)
TP3,1,ROMSEL_N,TestPoint_Pad_D1.0mm,not assembled (pads only)
TP4,1,ROMSEL_EXP,TestPoint_Pad_D1.0mm,not assembled (pads only)
TP5,1,OE_N,TestPoint_Pad_D1.0mm,not assembled (pads only)
TP6,1,EN_N,TestPoint_Pad_D1.0mm,not assembled (pads only)
TP7,1,GAME,TestPoint_Pad_D1.0mm,not assembled (pads only)
TP8,1,IRQ_N,TestPoint_Pad_D1.0mm,not assembled (pads only)
U1,1,RP2350_80QFN,RP2350-QFN-80-1EP_10x10_P0.4mm_EP3.4x3.4mm_ThermalVias,
U3,1,W25Q128JVS,SOIC-8_5.23x5.23mm_P1.27mm,
U4,1,DNF,SOIC-8_5.23x5.23mm_P1.27mm,
U10 U11 U12 U13,4,74LVC245,TSSOP-20_4.4x6.5mm_P0.65mm,
U14,1,74HCT32,TSSOP-14_4.4x5mm_P0.65mm,
U15,1,74HC04,TSSOP-14_4.4x5mm_P0.65mm,
U16,1,AP2112K-3.3,SOT-23-5,
U17,1,74LVC1G02,SOT-23-5,
Y1,1,ABM8-272-T3,Crystal_SMD_3225-4Pin_3.2x2.5mm,
